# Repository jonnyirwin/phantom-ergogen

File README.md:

> ⚠️ **Work in progress — do not build this yet.** The PCB, case, and firmware have not been validated against a physical build. Things will change, things may be wrong. Watch the commits if you want to follow along, but don't order boards from these files yet.

# Eidolon

> **eidolon** /aɪˈdoʊlɒn/ *noun*
> An idealized image; a phantom or spectre of a person or thing.
> — from Greek εἴδωλον *(image, idol, phantom)*

---

A small column-staggered wireless split keyboard. 30 keys (5×3 + 2 thumb per half), Kailh Choc v1 switches, Seeed XIAO nRF52840 BLE, Totem-style clamshell case. Both halves are independent wireless units — no TRRS cable.

## Built on the shoulders of

| Keyboard | Role in this project |
|----------|----------------------|
| [**Phantom**](https://github.com/davidphilipbarr/Phantom) by davidphilipbarr | PCB layout source — key positions reverse-engineered from `lephantom.kicad_pcb`; board outline traced from the original `Edge.Cuts`. Eidolon matches the original key centres to < 0.15 mm. |
| [**TOTEM**](https://github.com/GEIGEIGEIST/TOTEM) by GEIGEIGEIST | Case design reference — switch hole dimensions, keycap recess depth, clamshell geometry, and hot-swap socket pocket profiles from the Totem STEP file; the XIAO BLE SMD footprint (`pcb/footprints/xiao_ble.js`) is adapted from Totem's `xiao-ble-smd-cutout`. |
| [**Rufous**](https://github.com/jcmkk3/trochilidae/) by jcmkk3 | Diode placement — diodes sit in each Choc south LED cutout following the Rufous approach. (`pcb/footprints/xiao_pogo.js`, a pogo-pin XIAO mount adapted from Rufous, is kept as an unused alternative to the SMD footprint.) |

## PCB

| Left half | Right half |
|-----------|-----------|
|  |  |

## Case

| Top — left | Top — right |
|------------|-------------|
|  |  |

| Bottom — left | Bottom — right |
|---------------|----------------|
|  |  |

---

## Repository layout

```
pcb/              Ergogen source + routed KiCad files + gerbers
  eidolon.yaml      Ergogen config (geometry + nets)
  footprints/       custom Ergogen footprints
  build.js          local build wrapper (injects footprints)
  eidolon_left.kicad_pcb   routed left half
  eidolon_right.kicad_pcb  routed right half
  eidolon_left_gerbers.zip
  eidolon_right_gerbers.zip

case/             OpenSCAD case design
  eidolon_case.scad        top shell (both halves via -D right=true)
  eidolon_case_bottom.scad bottom shell
  stl/                     pre-generated STL files
```

---

## PCB build (Ergogen)

Custom footprints live in `pcb/footprints/`, so use the wrapper rather than the ergogen CLI directly:

```sh
cd pcb
npm install       # once
node build.js     # -> pcb/output/
```

Outputs land in `pcb/output/`:
- `outlines/board_left.svg|dxf`, `board_right.svg|dxf` — board perimeters
- `pcbs/eidolon_left.kicad_pcb`, `eidolon_right.kicad_pcb` — both halves, footprints + nets placed (no routes)

On **ergogen.xyz**, paste each file in `pcb/footprints/` into the web app's Footprints section under its filename (e.g. `reset_button`); `eidolon.yaml` then works as-is.

### Layout

```
 pinky  ring  middle index inner
   ·    top    top   top   ·       (pinky has no top row; inner has no bottom)
 home  home   home  home  upper
 bot   bot    bot   bot   lower
                  thumbL thumbR    (-8°)
```

Pinky splayed 5°, ring splayed 3°; other columns straight. Choc spacing: 18 mm columns, 17 mm rows.

### Wiring — COL2ROW diode matrix (XIAO BLE)

Each half is a fully independent wireless unit (own XIAO + battery, no TRRS), so the two halves carry **independent pin maps**. The columns are identical; the rows are assigned per half to keep each MCU's fan-out clean.

| Matrix | Net | XIAO pin (left) | XIAO pin (right) |
|--------|-----|-----------------|------------------|
| pinky col  | C0 | D0 | D0 |
| ring col   | C1 | D1 | D1 |
| middle col | C2 | D2 | D2 |
| index col  | C3 | D3 | D3 |
| inner col  | C4 | D4 | D4 |
| top row    | R0 | D5 | D10 |
| home row   | R1 | D6 | D9  |
| bottom row | R2 | D8 | D8  |
| thumb row  | R3 | D7 | D7  |

On the right half all four rows sit on the matrix-facing `D7`–`D10` edge (`D5`/`D6` spare), so only the five columns cross the MCU — the physical minimum. **The two halves therefore need different `MATRIX_ROW_PINS` in firmware.**

Power: battery + → `RAW_BATT` → slide switch → `BATT` → XIAO `B+`; battery − → GND.

> **Verify before fab:** the XIAO pad→pin mapping lives in `pcb/footprints/xiao_ble.js` (surface-mount, mounted **face-up** over the PCB). It was corrected and checked against the XIAO datasheet and the TOTEM `xiao-ble-smd-cutout` footprint — re-confirm before ordering.

### Mirrored halves, not reversible

The original Phantom is a single reversible PCB flipped for both hands. Eidolon generates a true left and right board. Because each half is an independent wireless unit with its own firmware, the halves do **not** share a pin map — the right half's `MATRIX_ROW_PINS` differ from the left's (see the per-half table above).

---

## Case (OpenSCAD)

`case/eidolon_case.scad` is the top shell for both halves. The right half is the left mirrored (`-D right=true`).

```sh
openscad -o case/stl/eidolon_case_top_left.stl  case/eidolon_case.scad
openscad -D right=true -o case/stl/eidolon_case_top_right.stl  case/eidolon_case.scad
openscad -o case/stl/eidolon_case_bottom_left.stl  case/eidolon_case_bottom.scad
openscad -D right=true -o case/stl/eidolon_case_bottom_right.stl  case/eidolon_case_bottom.scad
```

Pre-generated STLs are in `case/stl/`.

Top shell features: keycap recess field, stepped 13.8 mm Choc plate holes, XIAO pocket with acrylic window rebate + USB-C cutout, battery pocket, power-switch wall slot, M2 bolt pockets.

### Bottom shell

`case/eidolon_case_bottom.scad` nests inside the top from below. Geometry:

- z ∈ [−2.0, 0]: exterior plate (`floor_t` = 2.0 mm) matching the top case outer footprint
- z ∈ [0, 2.1]: nesting lip; PCB rests on the lip top at z = 2.1
- Per-switch hot-swap socket pockets cut into the lip — traced from the Kailh PG1350 socket silkscreen (plastic body **plus** both SMD pad rectangles), inflated by `socket_clr` = 0.6 mm
- Choc plastic-pin, power-switch-leg, and XIAO underside-joint clearance pockets in the lip
- M2 hex nut pockets (4.0 mm AF × 1.8 mm) at the four bolt positions
- Four Ø8.4 × 1.8 mm bumpon pockets in the underside (≥7.5 mm clear of the nut pockets)

### Mounting hardware

| Part | Spec | Count |
|------|------|-------|
| Socket cap bolt | M2 × 12 mm | 4 per half |
| Hex nut | M2 (4.0 mm AF) | 4 per half |

### MCU acrylic window

Cut a piece of 1.5 mm clear acrylic to drop into the XIAO rebate:

| Dimension | Size |
|-----------|------|
| Width | 20.3 mm |
| Length | 22.8 mm |
| Thickness | 1.5 mm |

Angle the acrylic, slip the +y edge under the square lip (lip A), press the −y edge down past the chamfered lip (lip B). Remove the bottom shell to access the MCU.

---

## Firmware

ZMK firmware for the Eidolon is available at [jonnyirwin/zmk-keyboard-eidolon](https://github.com/jonnyirwin/zmk-keyboard-eidolon).

---

## Deviations from the original Phantom

- **Mirrored L/R** instead of a single reversible board.
- **BLE only** — XIAO nRF52840, COL2ROW diode matrix, battery + slide switch; Pro Micro and TRRS removed.
- **Diodes top-side**, in each Choc south LED gap — hotswap sockets are the only underside component.
- **Trackball omitted.**
- Board outline is the original `Edge.Cuts` polygon with 1.5 mm corner fillets.

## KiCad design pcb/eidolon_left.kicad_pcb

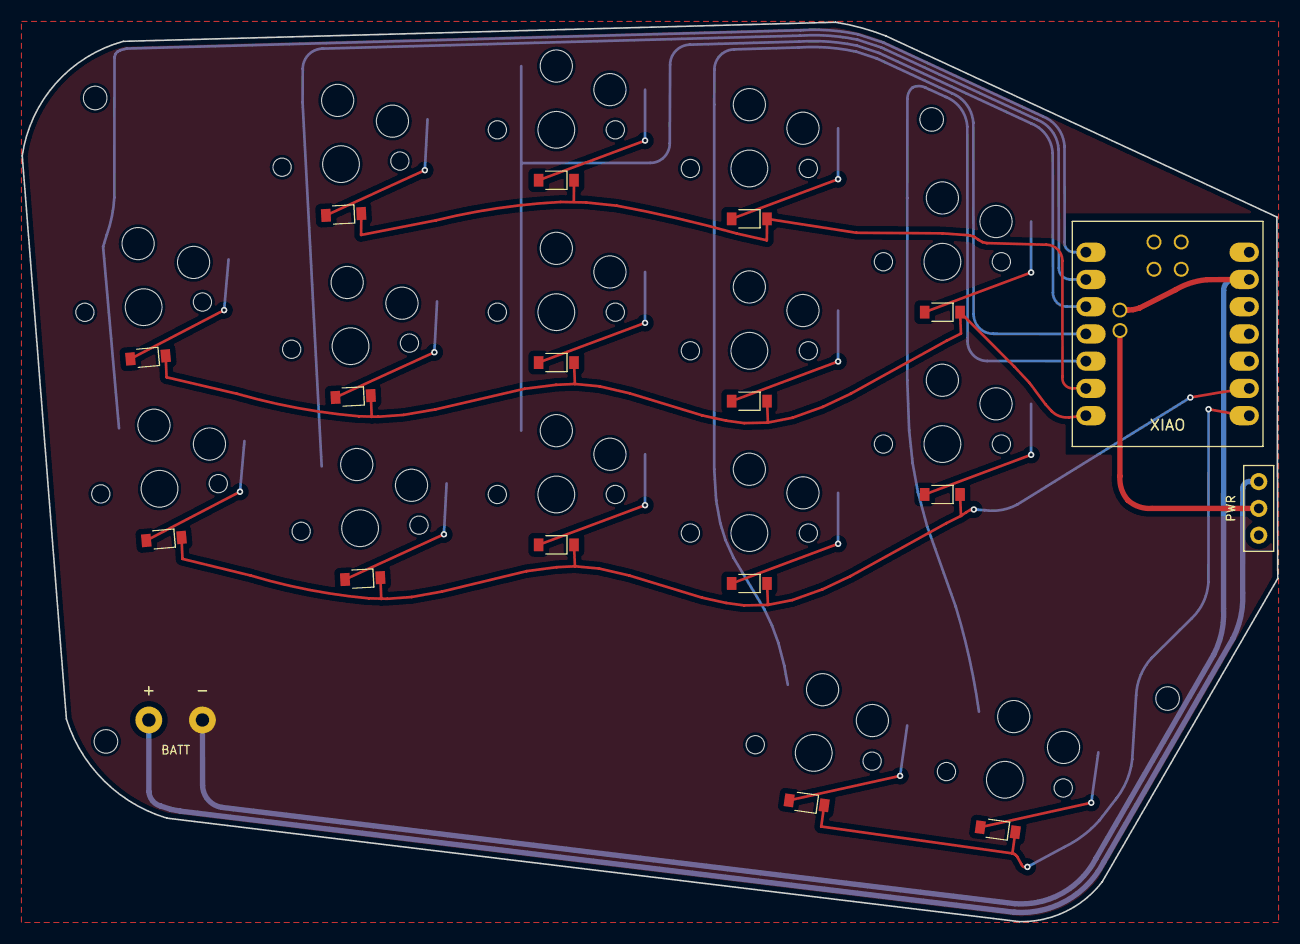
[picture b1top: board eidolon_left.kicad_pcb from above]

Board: 2 copper layers, 117.1 x 83.9 mm, 37 parts (0 on the bottom side), 27 nets.

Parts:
BT1: battery_pads
D1, D2, D3, D4, D5, D6, D7, D8, D9, D10, D11, D12, D13, D14, D15: diode_sod123
MCU1: xiao_ble
MH1, MH2, MH3, MH4: mounting_hole_m2
S1, S2, S3, S4, S5, S6, S7, S8, S9, S10, S11, S12, S13, S14, S15: PG1350
SW1: power_switch_spdt

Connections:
BATT: MCU1.BAT, SW1.2
C0: MCU1.1, S12.1, S13.1
C1: MCU1.2, S9.1, S10.1, S11.1
C2: MCU1.3, S1.1, S2.1, S3.1
C3: MCU1.4, S4.1, S5.1, S6.1, S14.1
C4: MCU1.5, S7.1, S8.1, S15.1
GND: BT1.2, MCU1.13, MCU1.GND
R0: D3.2, D6.2, D11.2, MCU1.6
R1: D2.2, D5.2, D8.2, D10.2, D13.2, MCU1.7
R2: D1.2, D4.2, D7.2, D9.2, D12.2, MCU1.9
R3: D14.2, D15.2, MCU1.8
RAW_BATT: BT1.1, SW1.1
matrix_index_bottom: D4.1, S4.2
matrix_index_home: D5.1, S5.2
matrix_index_top: D6.1, S6.2
matrix_inner_bottom: D7.1, S7.2
matrix_inner_home: D8.1, S8.2
matrix_middle_bottom: D1.1, S1.2
matrix_middle_home: D2.1, S2.2
matrix_middle_top: D3.1, S3.2
pinky_pinky_bottom: D12.1, S12.2
pinky_pinky_home: D13.1, S13.2
ring_ring_bottom: D9.1, S9.2
ring_ring_home: D10.1, S10.2
ring_ring_top: D11.1, S11.2
thumb_left_thumb: D14.1, S14.2
thumb_right_thumb: D15.1, S15.2
